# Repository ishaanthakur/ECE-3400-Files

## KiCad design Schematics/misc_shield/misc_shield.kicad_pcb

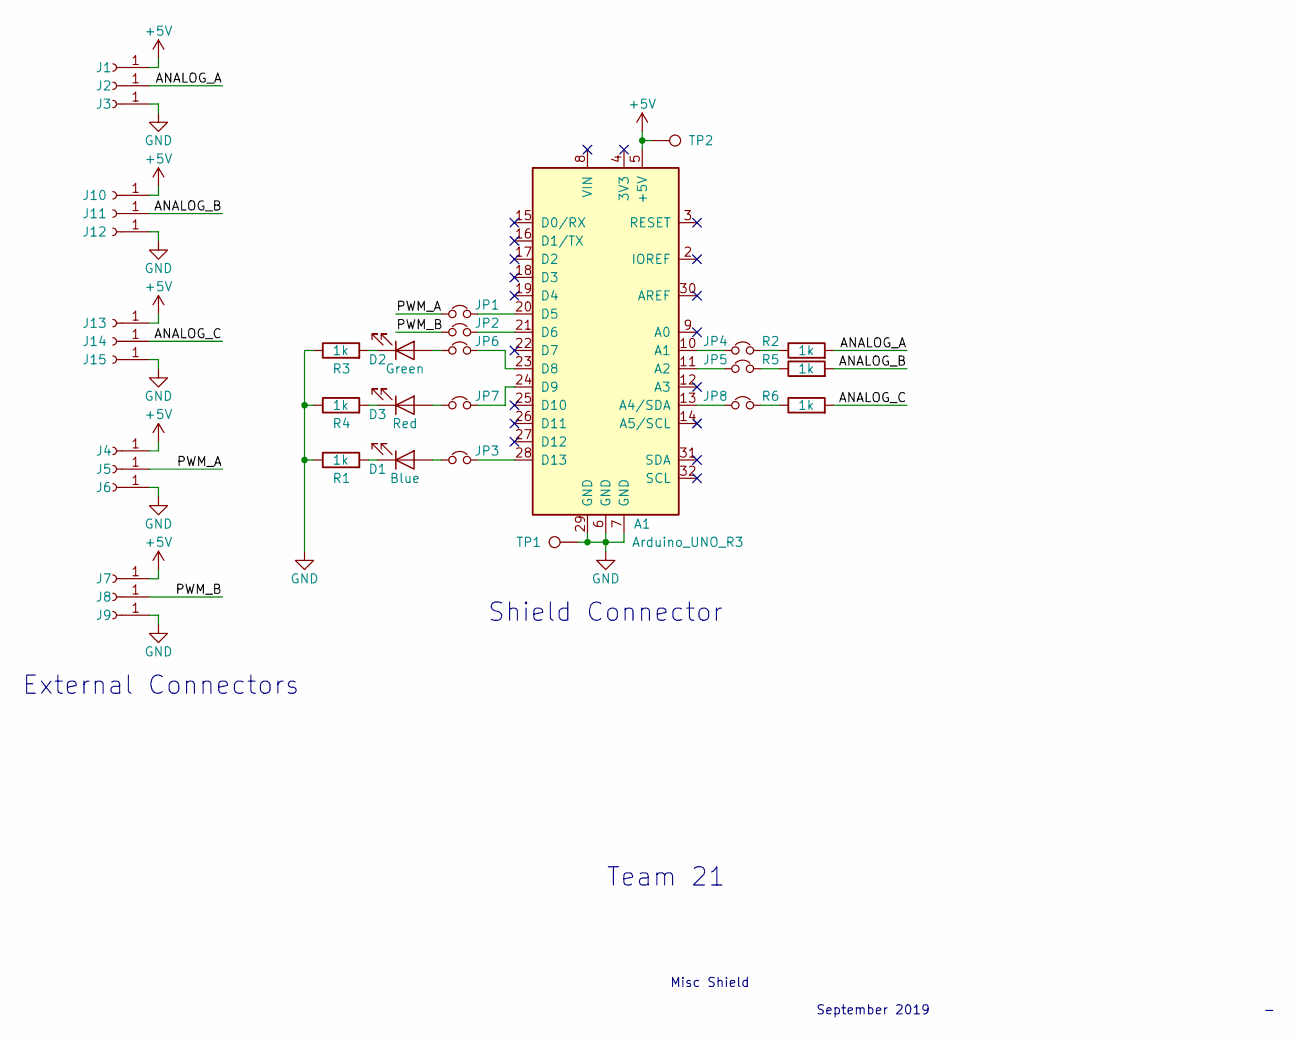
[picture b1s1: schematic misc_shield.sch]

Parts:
A1: Arduino_UNO_R3
D1: Blue; LED_5.0mm_Horizontal
D2: Green; LED_5.0mm_Horizontal
D3: Red; LED_5.0mm_Horizontal
J1, J2, J3, J4, J5, J6, J7, J8, J9, J10, J11, J12, J13, J14, J15: Conn_1x1_Female; PinSocket_1x1
JP1, JP2, JP3, JP4, JP5, JP6, JP7, JP8: Jumper
R1, R2, R3, R4, R5, R6: 1k; Resistor_THT
TP1, TP2: Test_Point

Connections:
+5V: A1.5 (+5V), J1.1, J4.1, J7.1, J10.1, J13.1, TP2.1
/ANALOG_A: J2.1, R2.2
/ANALOG_B: J11.1, R5.2
/ANALOG_C: J14.1, R6.2
/PWM_A: J5.1, JP1.1
/PWM_B: J8.1, JP2.1
GND: A1.6 (GND), A1.7 (GND), A1.29 (GND), J3.1, J6.1, J9.1, J12.1, J15.1, R1.1, R3.1, R4.1, TP1.1
unnamed: A1.10 (A1), JP4.1
unnamed: A1.11 (A2), JP5.1
unnamed: A1.13 (A4/SDA), JP8.1
unnamed: A1.20 (D5), JP1.2
unnamed: A1.21 (D6), JP2.2
unnamed: A1.23 (D8), JP6.2
unnamed: A1.24 (D9), JP7.2
unnamed: A1.28 (D13), JP3.2
unnamed: D1.1 (K), R1.2
unnamed: D1.2 (A), JP3.1
unnamed: D2.1 (K), R3.2
unnamed: D2.2 (A), JP6.1
unnamed: D3.1 (K), R4.2
unnamed: D3.2 (A), JP7.1
unnamed: JP4.2, R2.1
unnamed: JP5.2, R5.1
unnamed: JP8.2, R6.1

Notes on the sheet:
Team 21
Misc Shield
September 2019
Shield Connector
External Connectors

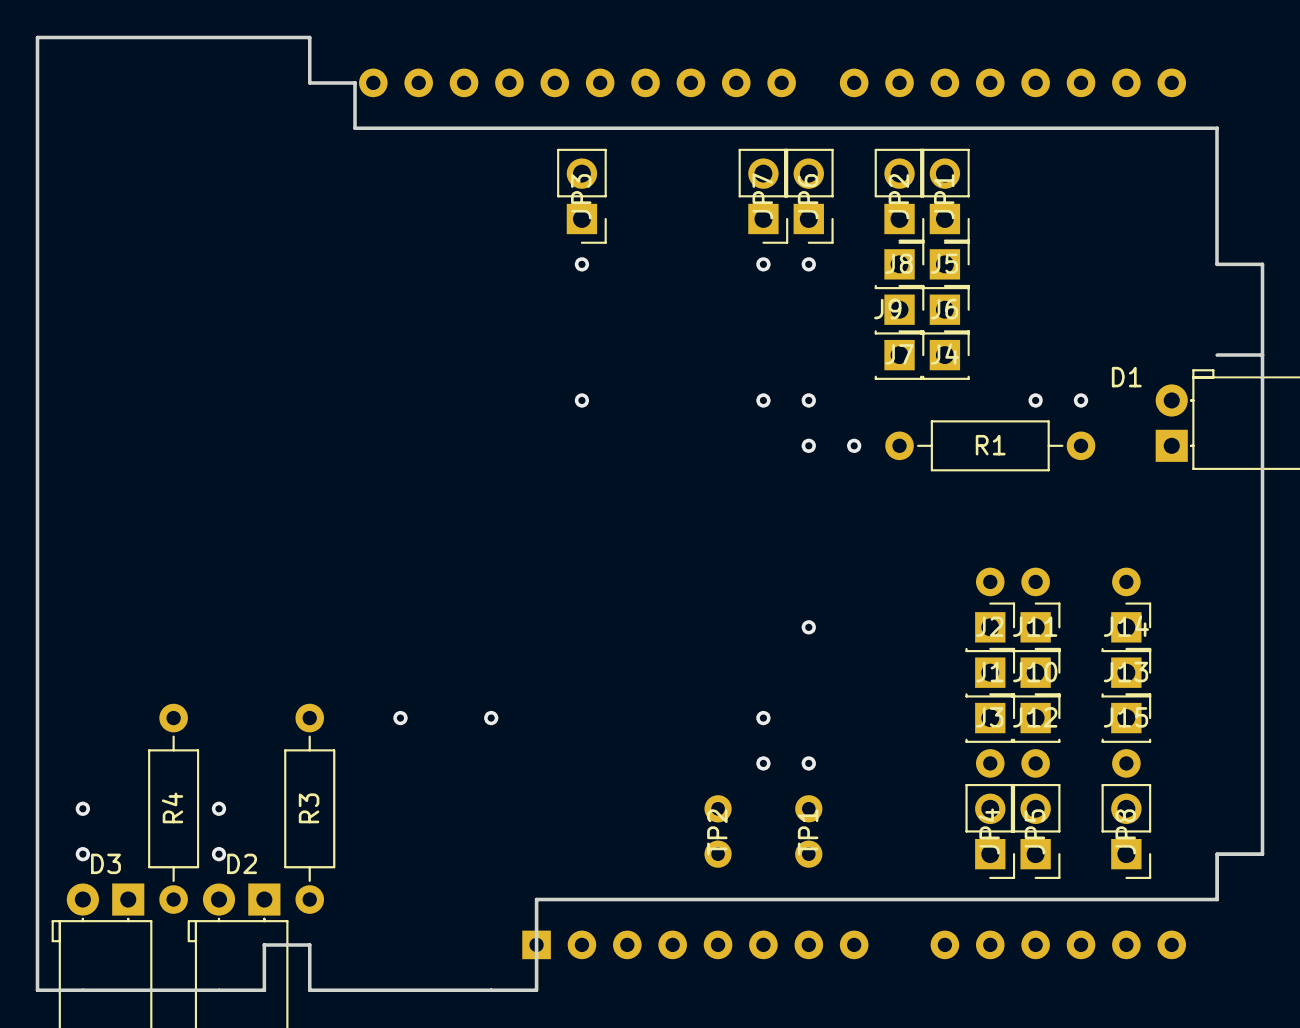
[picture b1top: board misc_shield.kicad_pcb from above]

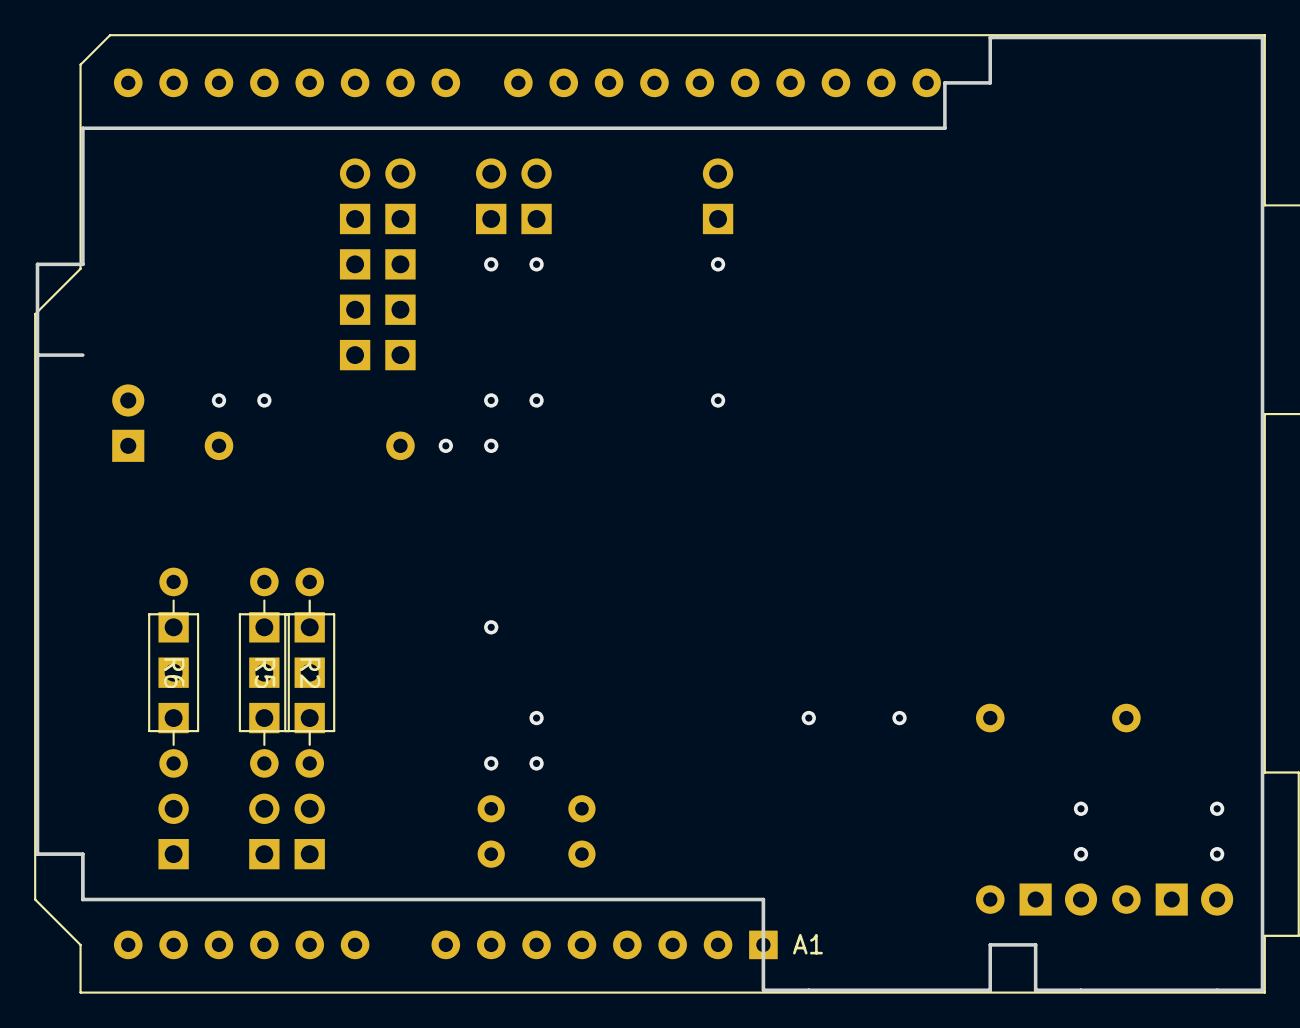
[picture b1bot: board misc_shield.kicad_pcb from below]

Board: 4 copper layers, 68.6 x 53.3 mm, 35 parts (4 on the bottom side), 24 nets.

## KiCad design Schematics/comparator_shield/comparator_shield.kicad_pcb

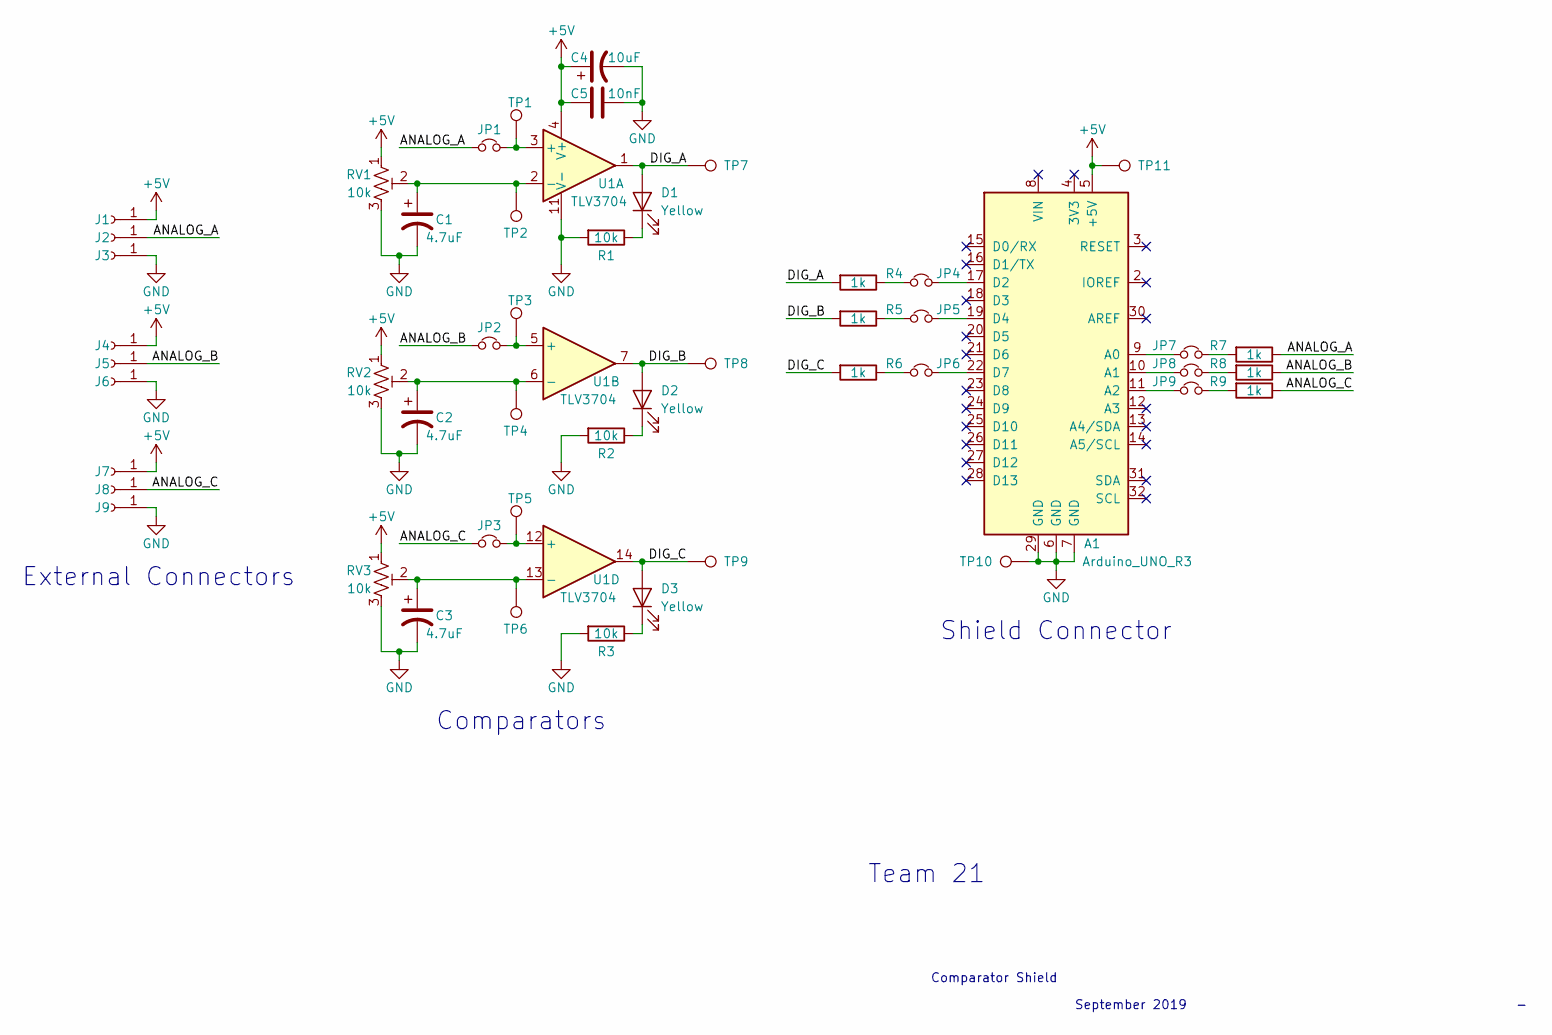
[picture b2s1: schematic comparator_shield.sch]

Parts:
A1: Arduino_UNO_R3
C1, C2, C3: 4.7uF; CP_4mm
C4: 10uF; CP_4mm
C5: 10nF; C_Ceramic
D1, D2, D3: Yellow; LED_5.0mm_Horizontal
J1, J2, J3, J4, J5, J6, J7, J8, J9: Conn_1x1_Female; PinSocket_1x1
JP1, JP2, JP3, JP4, JP5, JP6, JP7, JP8, JP9: Jumper
R1, R2, R3: 10k; Resistor_THT
R4, R5, R6, R7, R8, R9: 1k; R_0805
RV1, RV2, RV3: 10k; Trimmer
TP1, TP2, TP3, TP4, TP5, TP6, TP7, TP8, TP9, TP10, TP11: Test_Point
U1: TLV3704; DIP-14

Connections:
+5V: A1.5 (+5V), C4.1, C5.2, J1.1, J4.1, J7.1, RV1.1, RV2.1, RV3.1, TP11.1, U1.4 (V+)
/ANALOG_A: J2.1, JP1.1, R7.1
/ANALOG_B: J5.1, JP2.1, R8.1
/ANALOG_C: J8.1, JP3.1, R9.1
/DIG_A: D1.2 (A), R4.2, TP7.1, U1.1
/DIG_B: D2.2 (A), R5.2, TP8.1, U1.7
/DIG_C: D3.2 (A), R6.2, TP9.1, U1.14
GND: A1.6 (GND), A1.7 (GND), A1.29 (GND), C1.2, C2.2, C3.2, C4.2, C5.1, J3.1, J6.1, J9.1, R1.2, R2.2, R3.2, RV1.3, RV2.3, RV3.3, TP10.1, U1.11 (V-)
unnamed: A1.9 (A0), JP7.1
unnamed: A1.10 (A1), JP8.1
unnamed: A1.11 (A2), JP9.1
unnamed: A1.17 (D2), JP4.2
unnamed: A1.19 (D4), JP5.2
unnamed: A1.22 (D7), JP6.2
unnamed: C1.1, RV1.2, TP2.1, U1.2 (-)
unnamed: C2.1, RV2.2, TP4.1, U1.6 (-)
unnamed: C3.1, RV3.2, TP6.1, U1.13 (-)
unnamed: D1.1 (K), R1.1
unnamed: D2.1 (K), R2.1
unnamed: D3.1 (K), R3.1
unnamed: JP1.2, TP1.1, U1.3 (+)
unnamed: JP2.2, TP3.1, U1.5 (+)
unnamed: JP3.2, TP5.1, U1.12 (+)
unnamed: JP4.1, R4.1
unnamed: JP5.1, R5.1
unnamed: JP6.1, R6.1
unnamed: JP7.2, R7.2
unnamed: JP8.2, R8.2
unnamed: JP9.2, R9.2

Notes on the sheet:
Team 21
Comparator Shield
September 2019
Shield Connector
Comparators
External Connectors

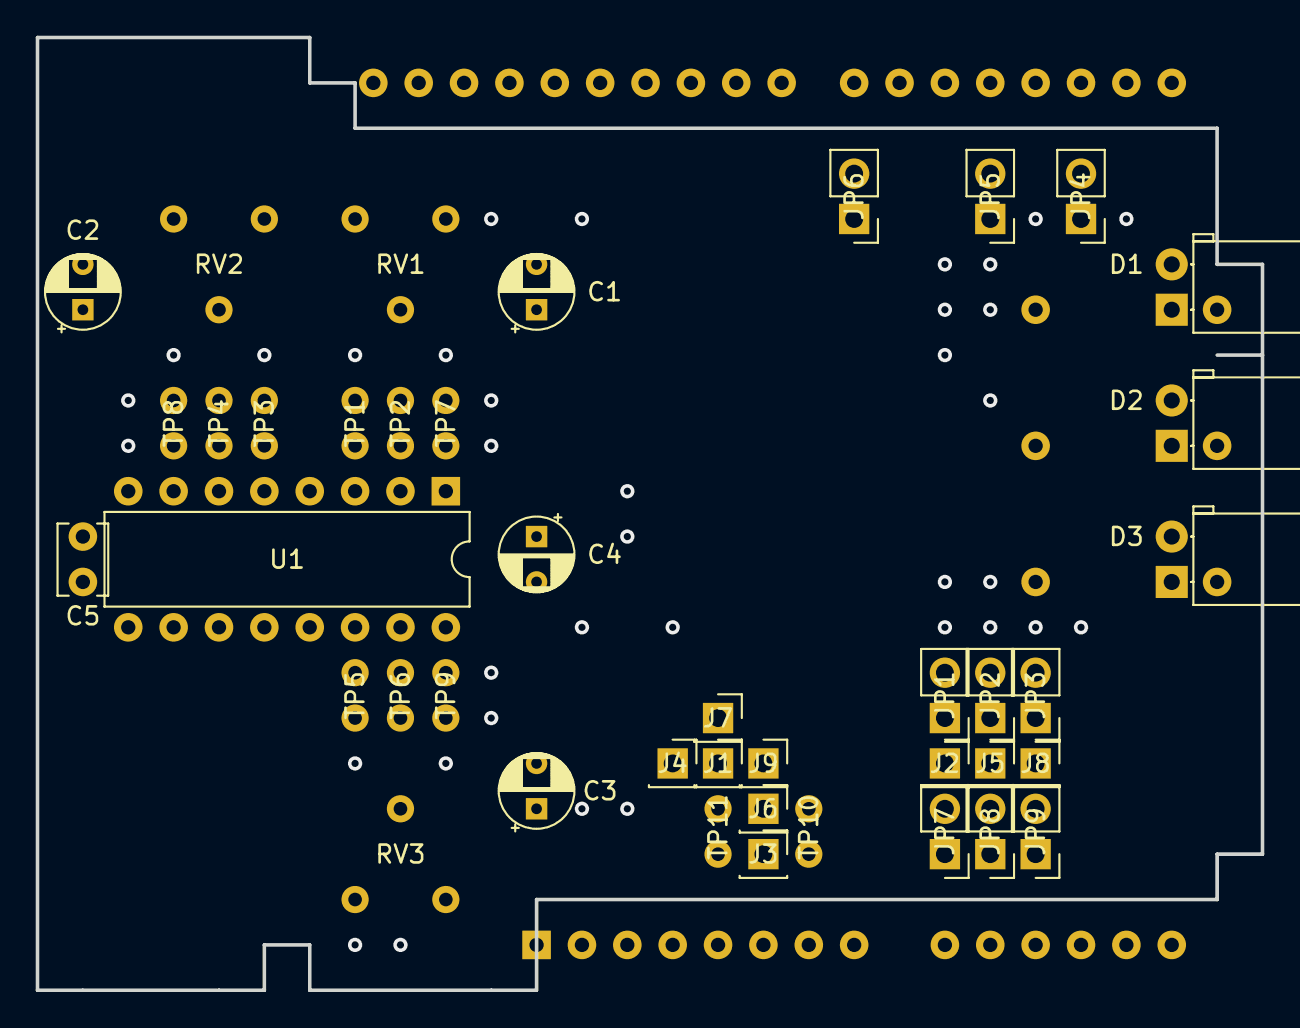
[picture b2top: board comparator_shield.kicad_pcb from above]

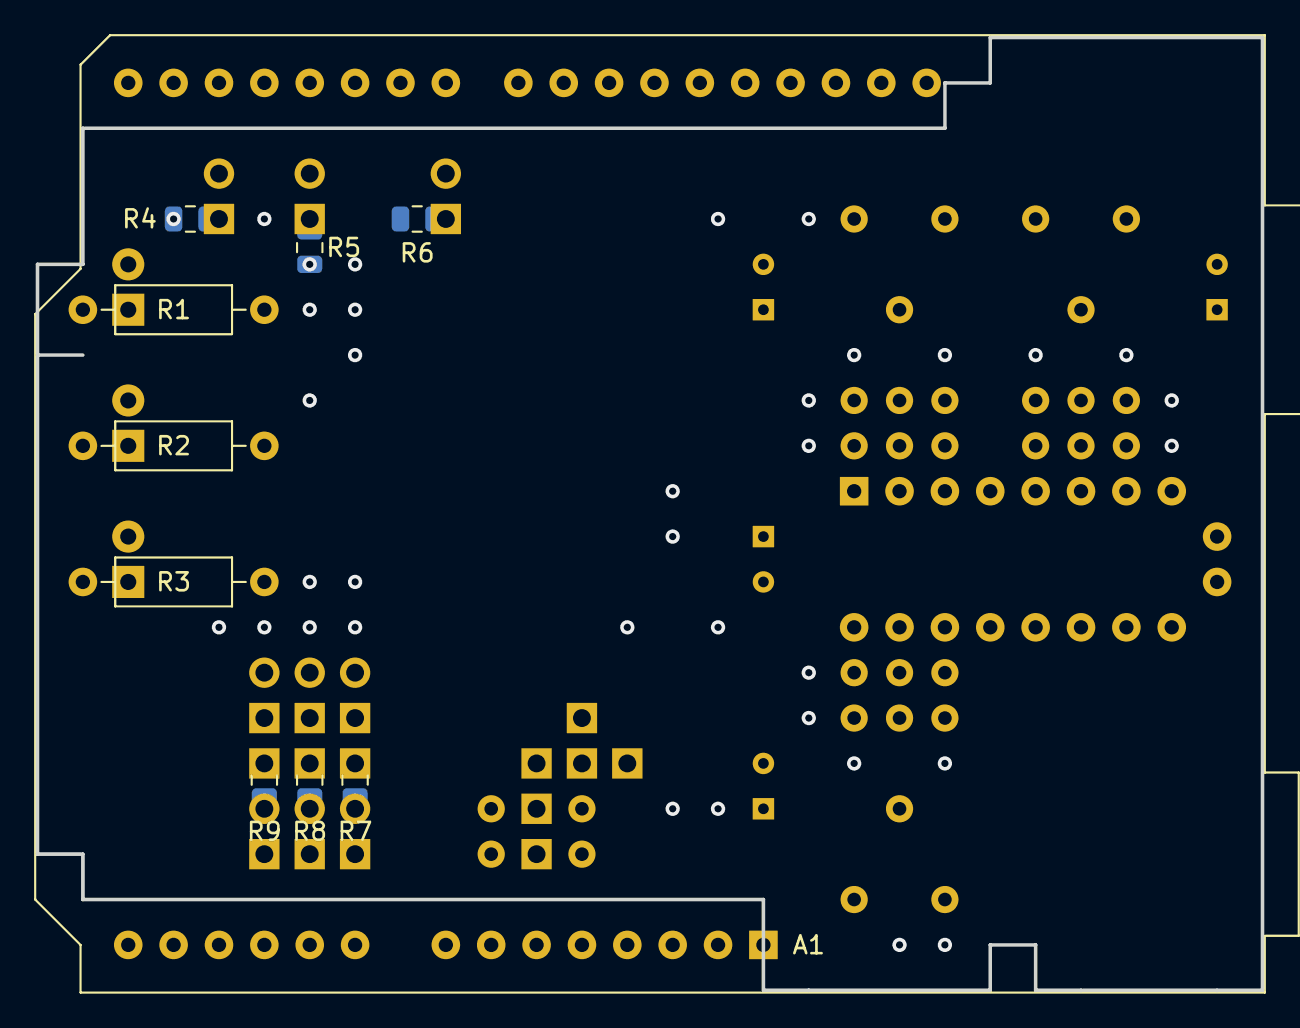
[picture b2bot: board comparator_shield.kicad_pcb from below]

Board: 4 copper layers, 68.6 x 53.3 mm, 51 parts (10 on the bottom side), 29 nets.

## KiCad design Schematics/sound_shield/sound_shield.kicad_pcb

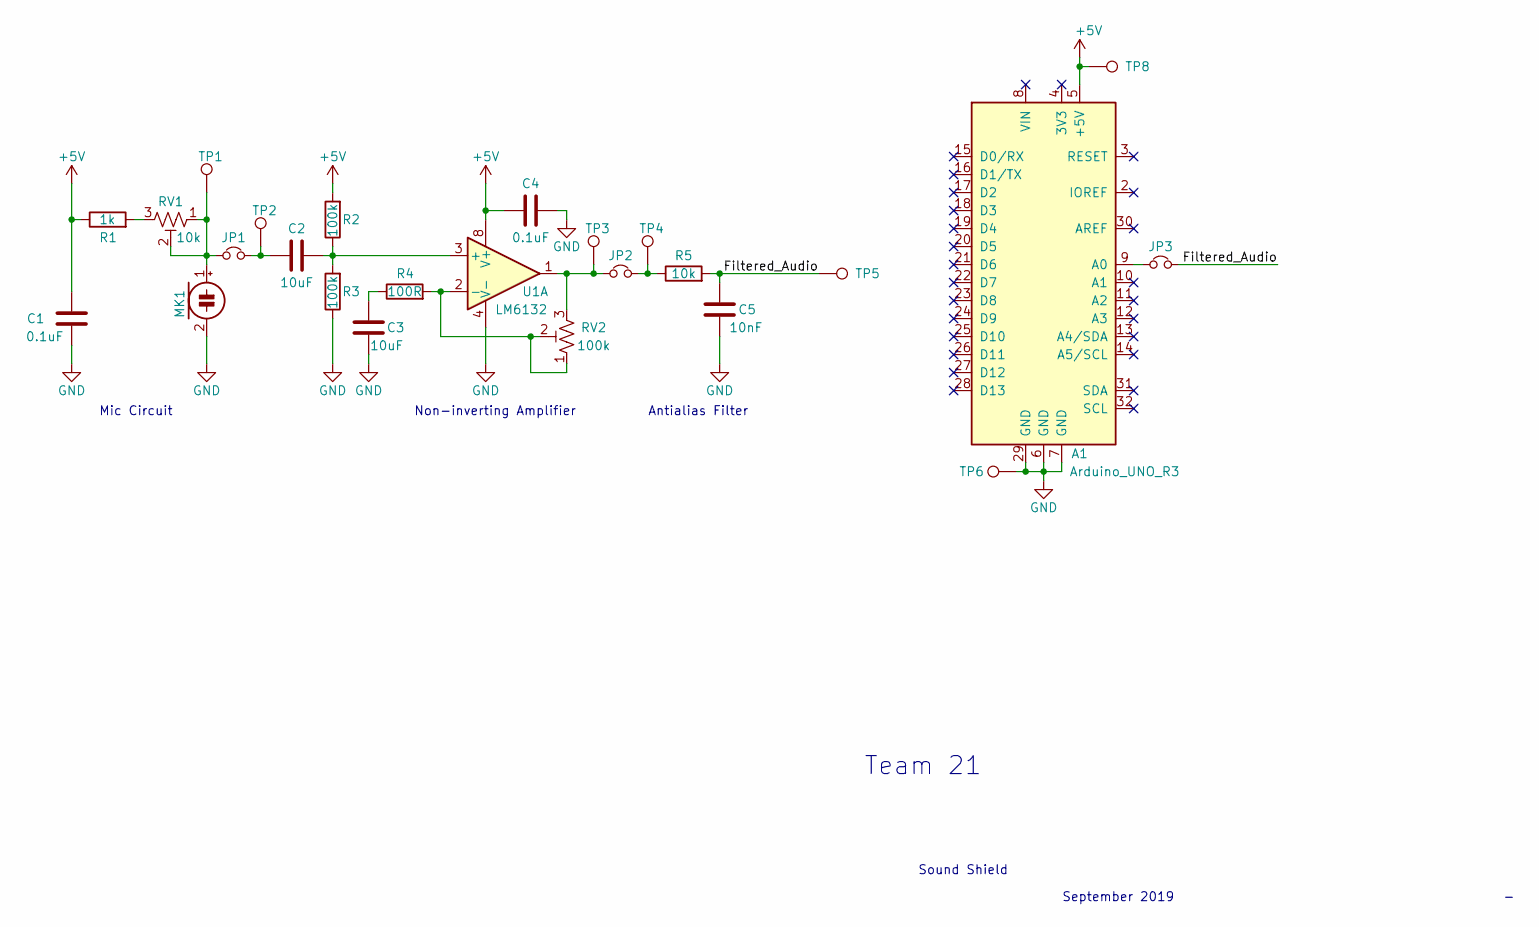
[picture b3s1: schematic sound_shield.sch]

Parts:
A1: Arduino_UNO_R3
C1, C4: 0.1uF; C_Ceramic
C2, C3: 10uF; C_0805
C5: 10nF; C_Ceramic
JP1, JP2, JP3: Jumper
MK1: Mic_Electret; Mic_Electret_10mm
R1: 1k; R_0805
R2, R3: 100k; Resistor_THT
R4: 100R; Resistor_THT
R5: 10k; Resistor_THT
RV1: 10k; Trimmer
RV2: 100k; Trimmer
TP1, TP2, TP3, TP4, TP5, TP6, TP8: Test_Point
U1: LM6132; DIP-8

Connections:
+5V: A1.5 (+5V), C1.2, C4.2, R1.1, R2.2, TP8.1, U1.8 (V+)
/Filtered_Audio: C5.1, JP3.2, R5.2, TP5.1
GND: A1.6 (GND), A1.7 (GND), A1.29 (GND), C1.1, C3.1, C4.1, C5.2, MK1.2 (-), R3.1, TP6.1, U1.4 (V-)
unnamed: A1.9 (A0), JP3.1
unnamed: C2.1, JP1.2, TP2.1
unnamed: C2.2, R2.1, R3.2, U1.3 (+)
unnamed: C3.2, R4.1
unnamed: JP1.1, MK1.1 (+), RV1.1, RV1.2, TP1.1
unnamed: JP2.1, RV2.3, TP3.1, U1.1
unnamed: JP2.2, R5.1, TP4.1
unnamed: R1.2, RV1.3
unnamed: R4.2, RV2.1, RV2.2, U1.2 (-)

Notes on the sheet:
Mic Circuit
Non-inverting Amplifier
Antialias Filter
Team 21
Sound Shield
September 2019

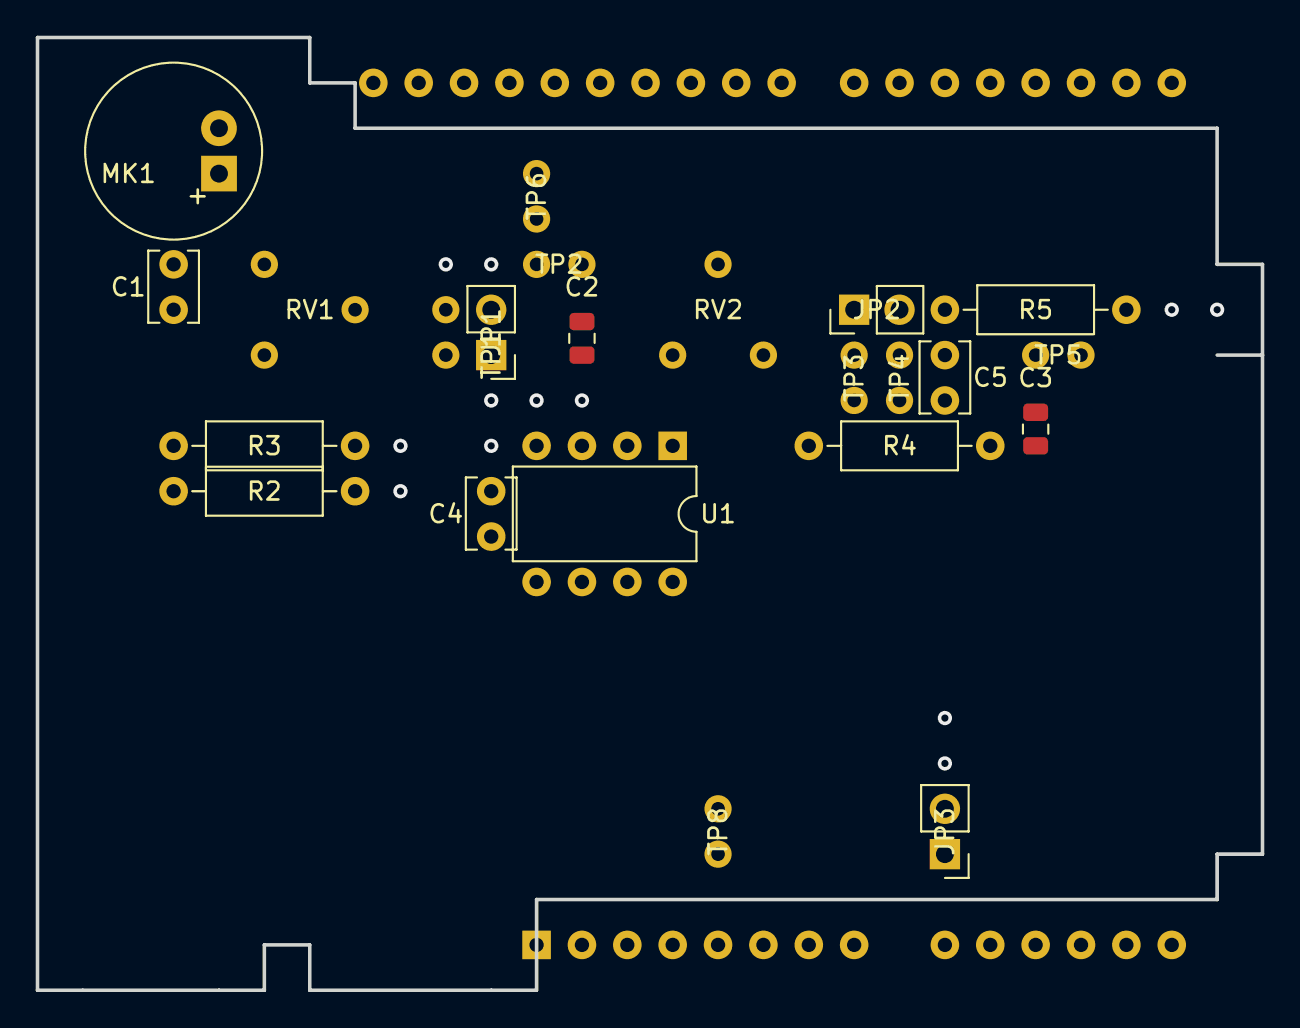
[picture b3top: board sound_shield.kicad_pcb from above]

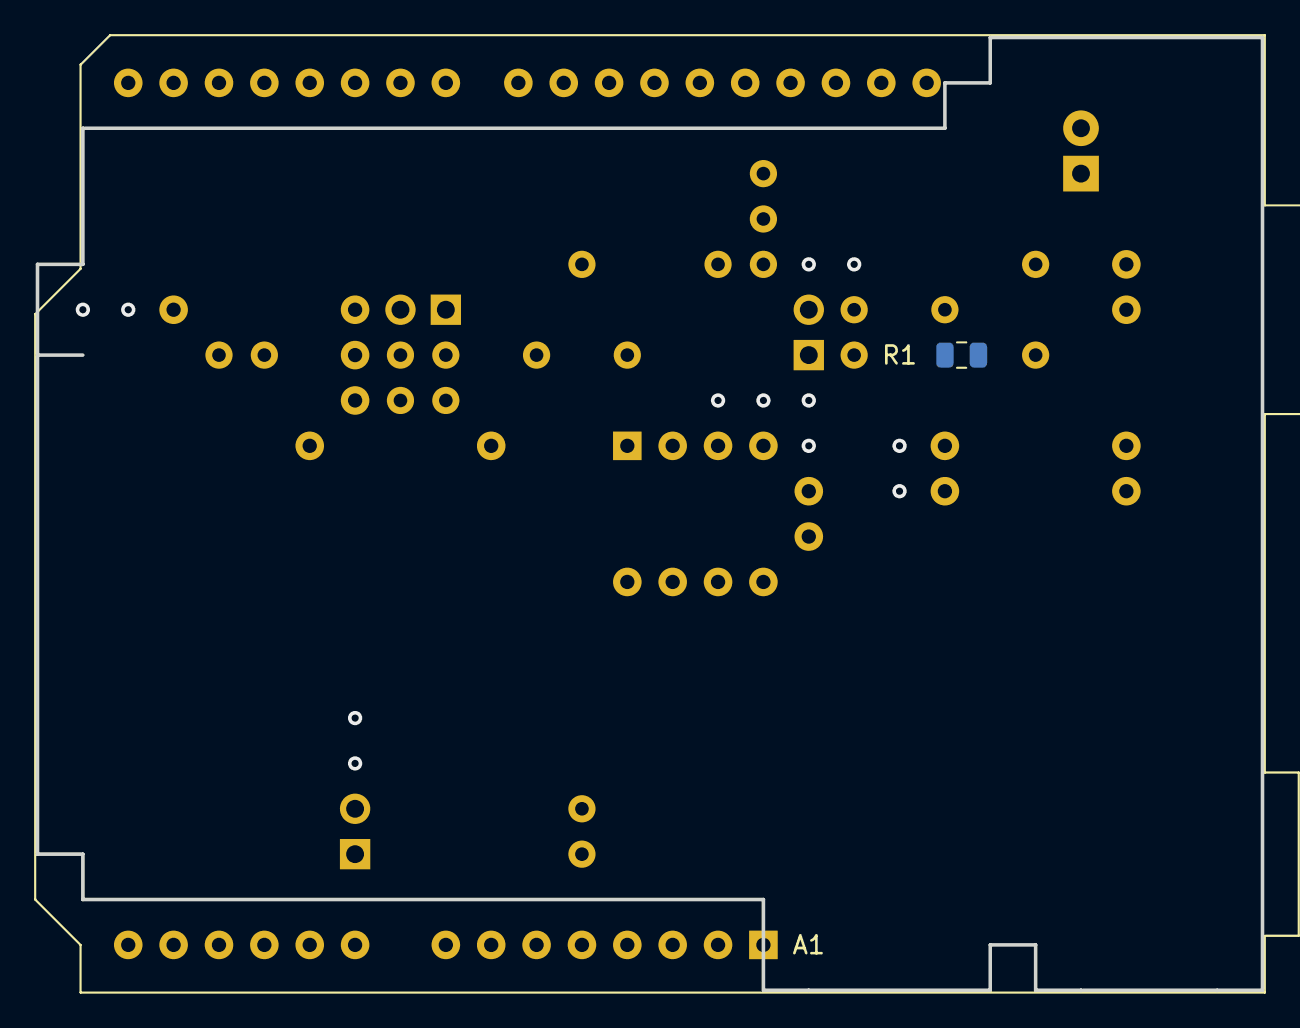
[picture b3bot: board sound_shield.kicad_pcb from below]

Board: 4 copper layers, 68.6 x 53.3 mm, 25 parts (2 on the bottom side), 12 nets.

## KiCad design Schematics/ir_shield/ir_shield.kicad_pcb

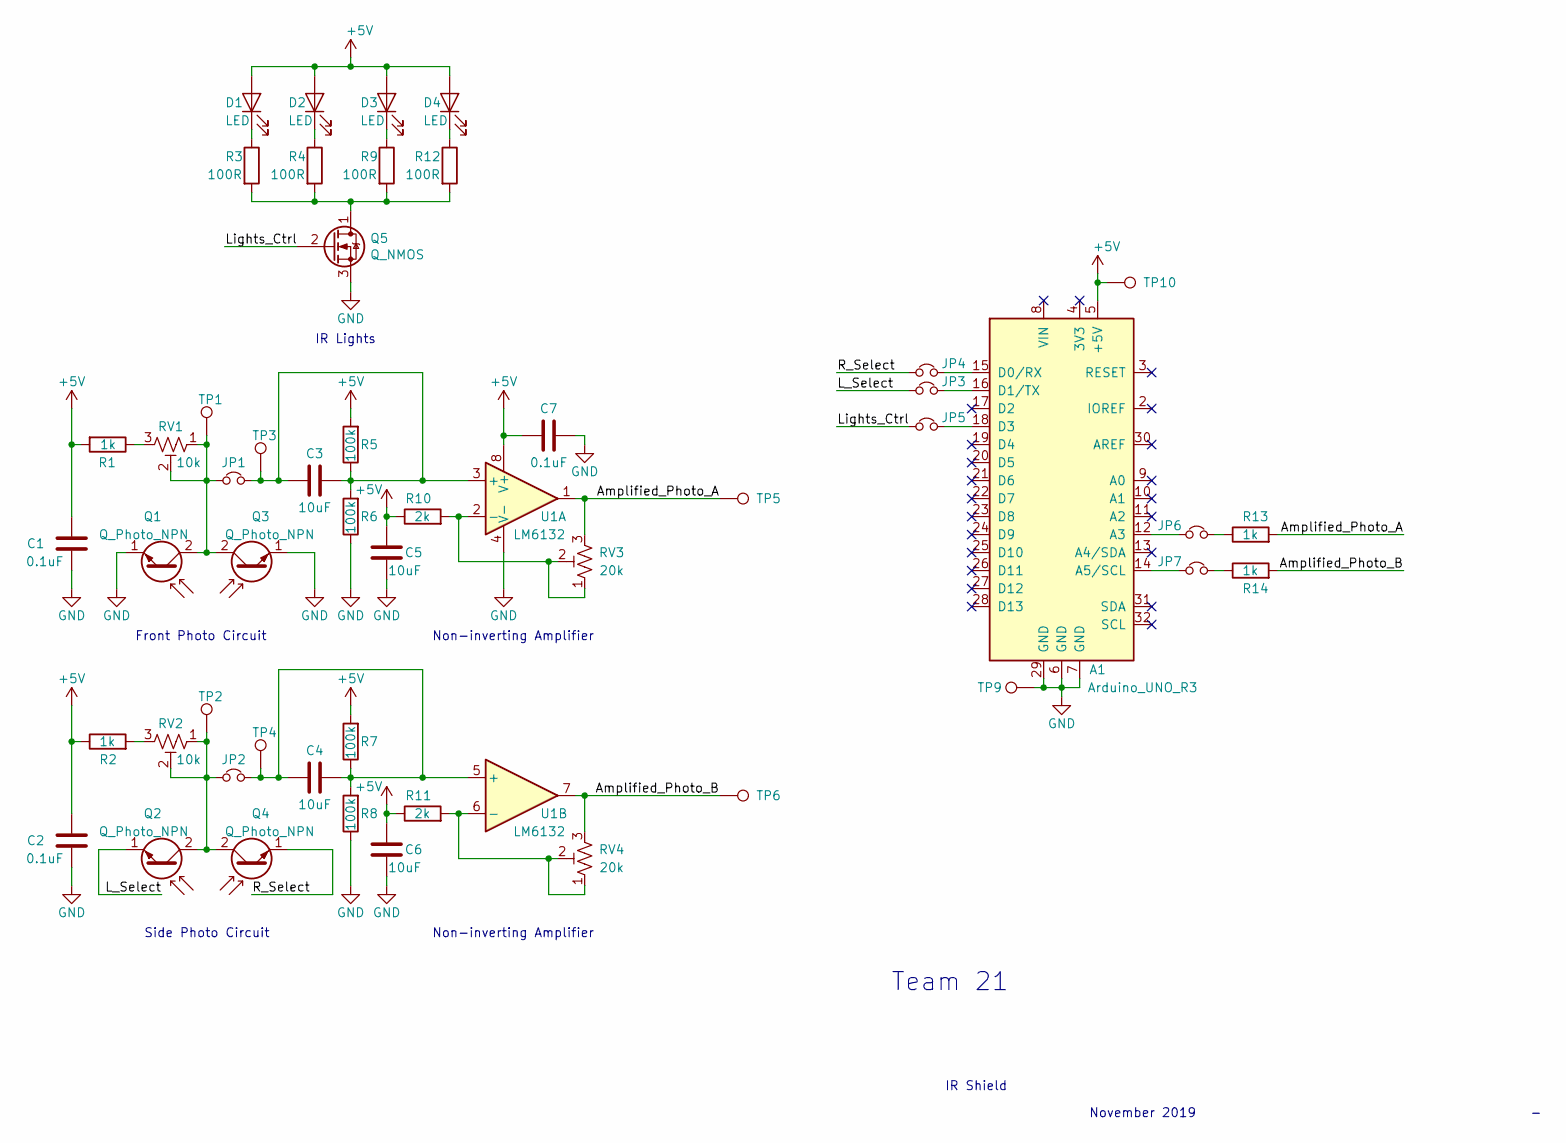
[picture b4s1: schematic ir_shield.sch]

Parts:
A1: Arduino_UNO_R3
C1, C2, C7: 0.1uF; C_Ceramic
C3, C4, C5, C6: 10uF; C_0805
D1, D2, D3, D4: LED; LED_5.0mm_Horizontal
JP1, JP2, JP3, JP4, JP5, JP6, JP7: Jumper
Q1, Q2, Q3, Q4: Q_Photo_NPN; PhotoNPN
Q5: Q_NMOS; TO-92
R1, R2, R13, R14: 1k; Resistor_THT_Vertical
R3, R4, R9, R12: 100R; Resistor_THT_Vertical
R5, R6, R7, R8: 100k; Resistor_THT_Vertical
R10, R11: 2k; Resistor_THT_Vertical
RV1, RV2: 10k; Trimmer
RV3, RV4: 20k; Trimmer
TP1, TP2, TP3, TP4, TP5, TP6, TP9, TP10: Test_Point
U1: LM6132; DIP-8

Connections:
+5V: A1.5 (+5V), C1.2, C2.2, C5.2, C6.2, C7.2, D1.2 (A), D2.2 (A), D3.2 (A), D4.2 (A), R1.2, R2.1, R5.2, R7.2, R10.1, R11.1, TP10.1, U1.8 (V+)
/Amplified_Photo_A: R13.2, RV3.3, TP5.1, U1.1
/Amplified_Photo_B: R14.2, RV4.3, TP6.1, U1.7
/L_Select: JP3.1, Q2.1 (E)
/Lights_Ctrl: JP5.1, Q5.2 (G)
/R_Select: JP4.1, Q4.1 (E)
GND: A1.6 (GND), A1.7 (GND), A1.29 (GND), C1.1, C2.1, C5.1, C6.1, C7.1, Q1.1 (E), Q3.1 (E), Q5.3 (S), R6.1, R8.1, TP9.1, U1.4 (V-)
unnamed: A1.12 (A3), JP6.1
unnamed: A1.14 (A5/SCL), JP7.1
unnamed: A1.15 (D0/RX), JP4.2
unnamed: A1.16 (D1/TX), JP3.2
unnamed: A1.18 (D3), JP5.2
unnamed: C3.1, C3.2, JP1.2, R5.1, R6.2, TP3.1, U1.3 (+)
unnamed: C4.1, C4.2, JP2.2, R7.1, R8.2, TP4.1, U1.5 (+)
unnamed: D1.1 (K), R3.1
unnamed: D2.1 (K), R4.1
unnamed: D3.1 (K), R9.1
unnamed: D4.1 (K), R12.1
unnamed: JP1.1, Q1.2 (C), Q3.2 (C), RV1.1, RV1.2, TP1.1
unnamed: JP2.1, Q2.2 (C), Q4.2 (C), RV2.1, RV2.2, TP2.1
unnamed: JP6.2, R13.1
unnamed: JP7.2, R14.1
unnamed: Q5.1 (D), R3.2, R4.2, R9.2, R12.2
unnamed: R1.1, RV1.3
unnamed: R2.2, RV2.3
unnamed: R10.2, RV3.1, RV3.2, U1.2 (-)
unnamed: R11.2, RV4.1, RV4.2, U1.6 (-)

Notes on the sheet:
Team 21
IR Shield
November 2019
IR Lights
Non-inverting Amplifier
Front Photo Circuit
Side Photo Circuit

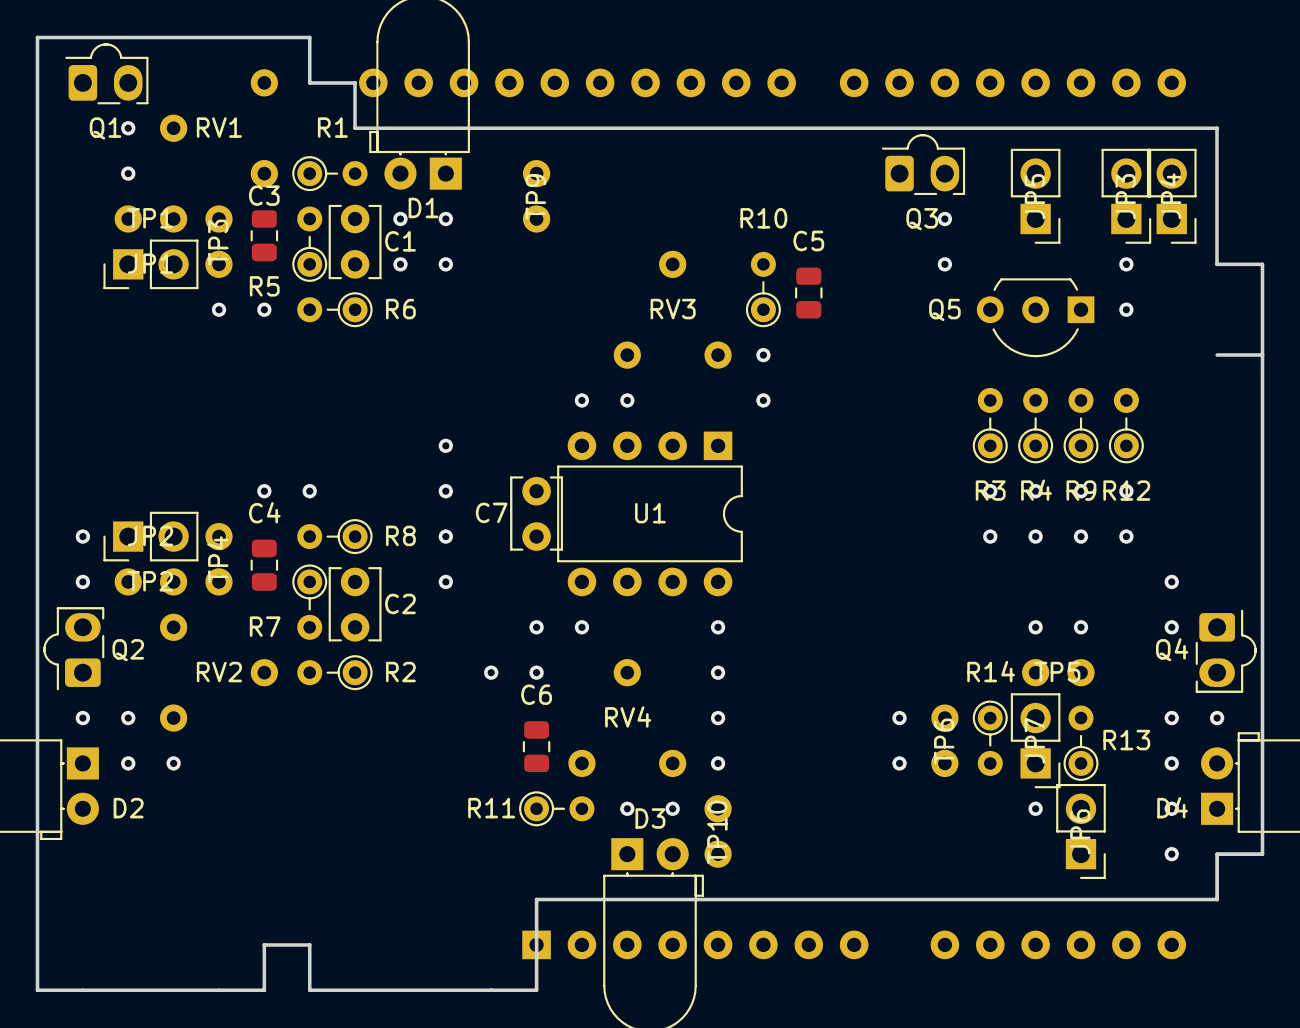
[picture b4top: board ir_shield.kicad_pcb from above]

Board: 4 copper layers, 68.6 x 53.3 mm, 51 parts (1 on the bottom side), 27 nets.

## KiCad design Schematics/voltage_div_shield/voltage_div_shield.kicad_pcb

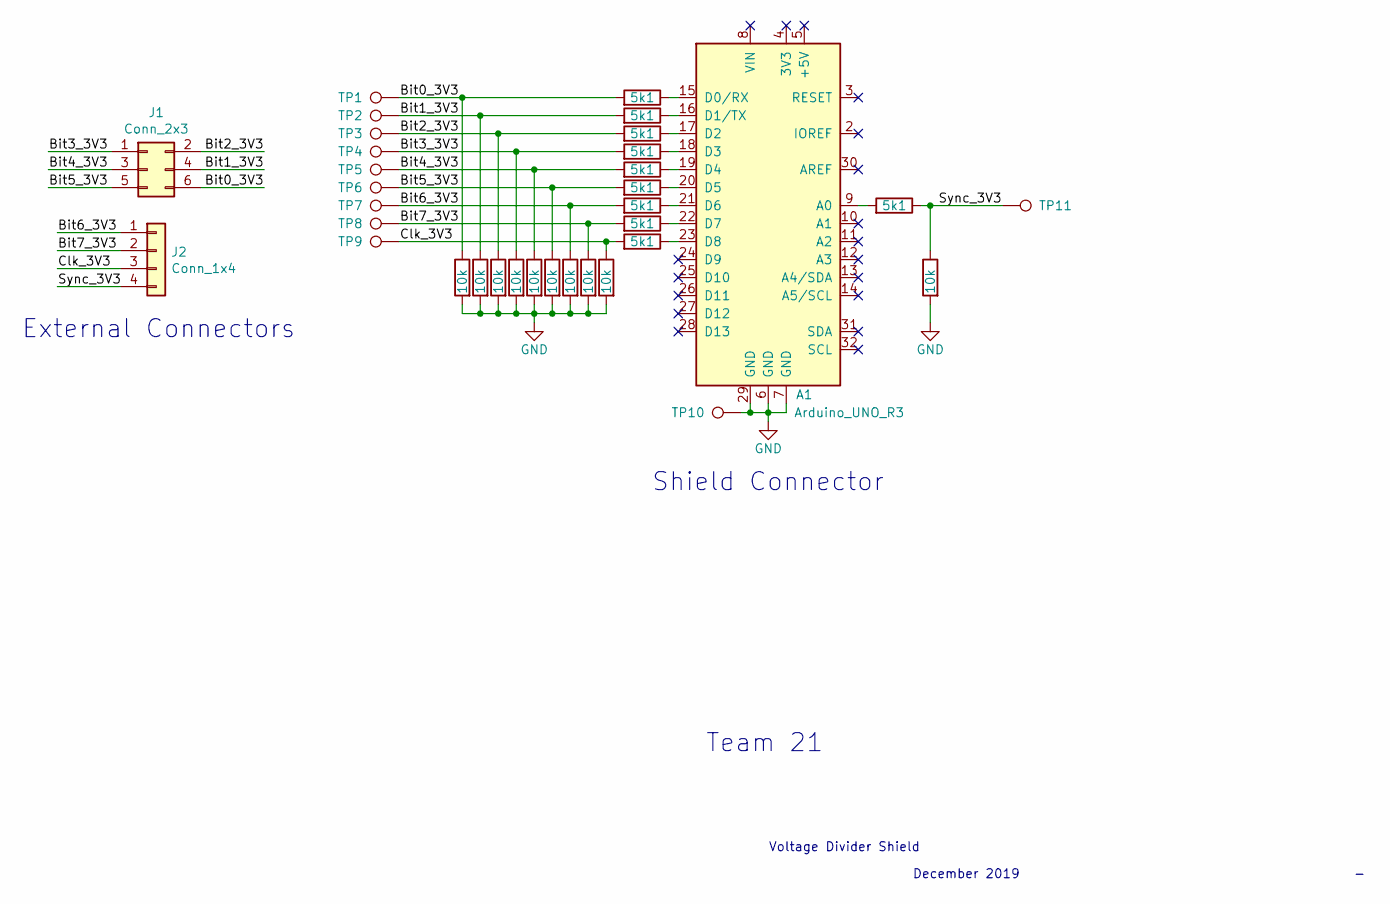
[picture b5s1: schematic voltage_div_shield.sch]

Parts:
A1: Arduino_UNO_R3
J1: Conn_2x3; PinHeader_2x3
J2: Conn_1x4; PinHeader_1x4
R1, R2, R3, R4, R5, R6, R7, R8, R9, R20: 10k; Resistor_THT
R10, R11, R12, R13, R14, R15, R16, R17, R18, R19: 5k1; Resistor_THT
TP1, TP2, TP3, TP4, TP5, TP6, TP7, TP8, TP9, TP10, TP11: Test_Point

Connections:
/Bit0_3V3: J1.6, R1.1, R10.2, TP1.1
/Bit1_3V3: J1.4, R2.1, R11.2, TP2.1
/Bit2_3V3: J1.2, R3.1, R12.2, TP3.1
/Bit3_3V3: J1.1, R4.1, R13.2, TP4.1
/Bit4_3V3: J1.3, R5.1, R14.2, TP5.1
/Bit5_3V3: J1.5, R6.1, R15.2, TP6.1
/Bit6_3V3: J2.1, R7.1, R16.2, TP7.1
/Bit7_3V3: J2.2, R8.1, R17.2, TP8.1
/Clk_3V3: J2.3, R9.1, R18.2, TP9.1
/Sync_3V3: J2.4, R19.1, R20.1, TP11.1
GND: A1.6 (GND), A1.7 (GND), A1.29 (GND), R1.2, R2.2, R3.2, R4.2, R5.2, R6.2, R7.2, R8.2, R9.2, R20.2, TP10.1
unnamed: A1.9 (A0), R19.2
unnamed: A1.15 (D0/RX), R10.1
unnamed: A1.16 (D1/TX), R11.1
unnamed: A1.17 (D2), R12.1
unnamed: A1.18 (D3), R13.1
unnamed: A1.19 (D4), R14.1
unnamed: A1.20 (D5), R15.1
unnamed: A1.21 (D6), R16.1
unnamed: A1.22 (D7), R17.1
unnamed: A1.23 (D8), R18.1

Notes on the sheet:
Team 21
Voltage Divider Shield
December 2019
Shield Connector
External Connectors

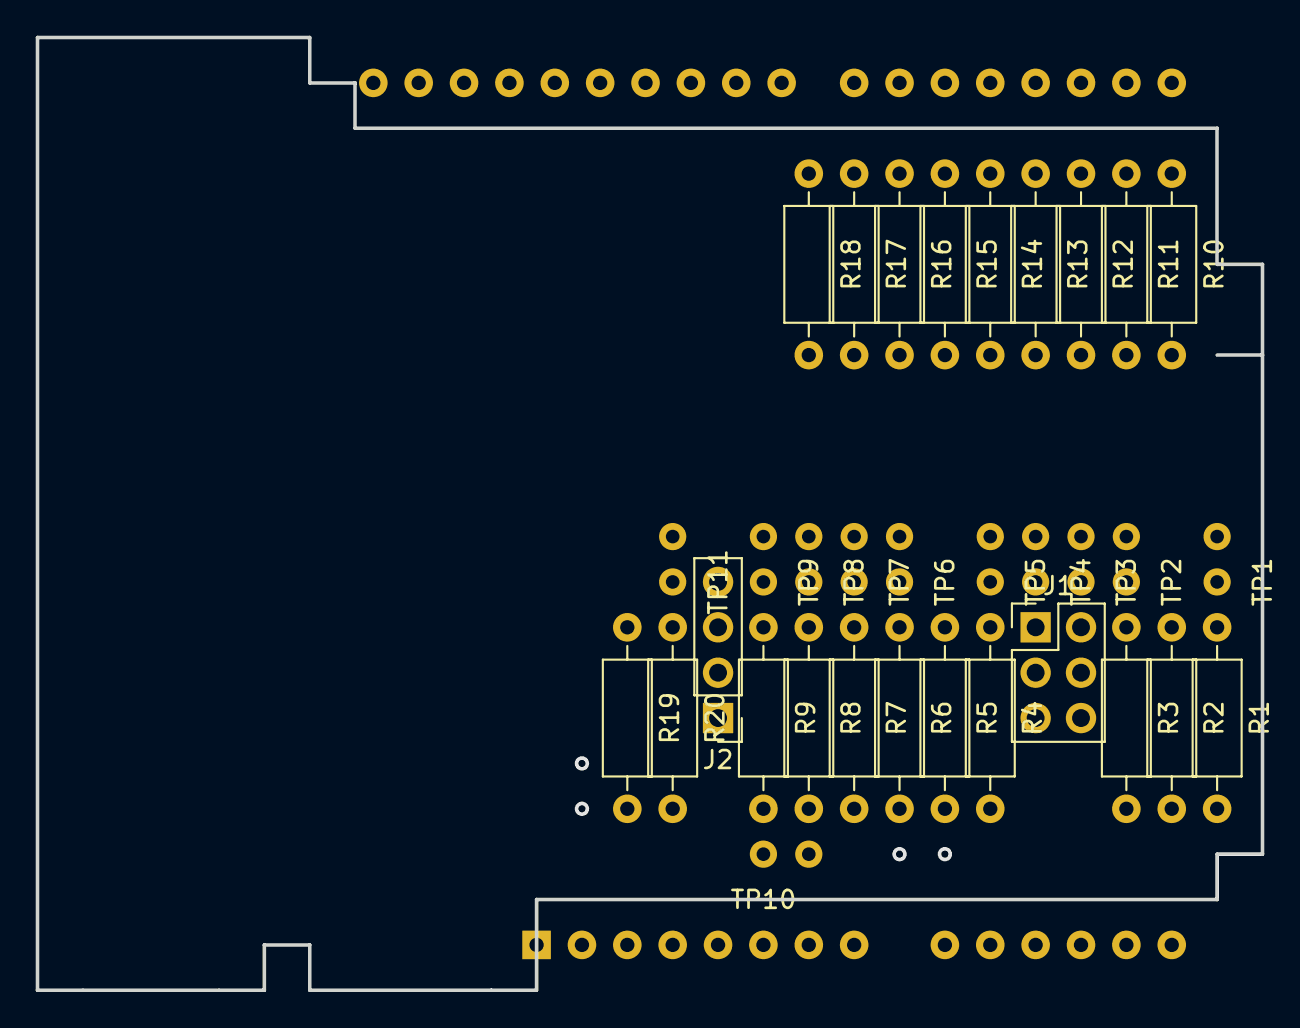
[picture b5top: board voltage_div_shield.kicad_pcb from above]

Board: 4 copper layers, 68.6 x 53.3 mm, 34 parts (1 on the bottom side), 21 nets.

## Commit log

2019-11-20 another one
2019-12-21 added some changes
